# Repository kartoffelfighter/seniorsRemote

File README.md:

# seniorsRemote
A very basic remote tv (IR) control for seniors (and lazy people like me)

# nightly branch
this branch is dangerous! push -f(uck) possible

# hwtest branch

nightlier than nightly branch - WIP hwtest firmware

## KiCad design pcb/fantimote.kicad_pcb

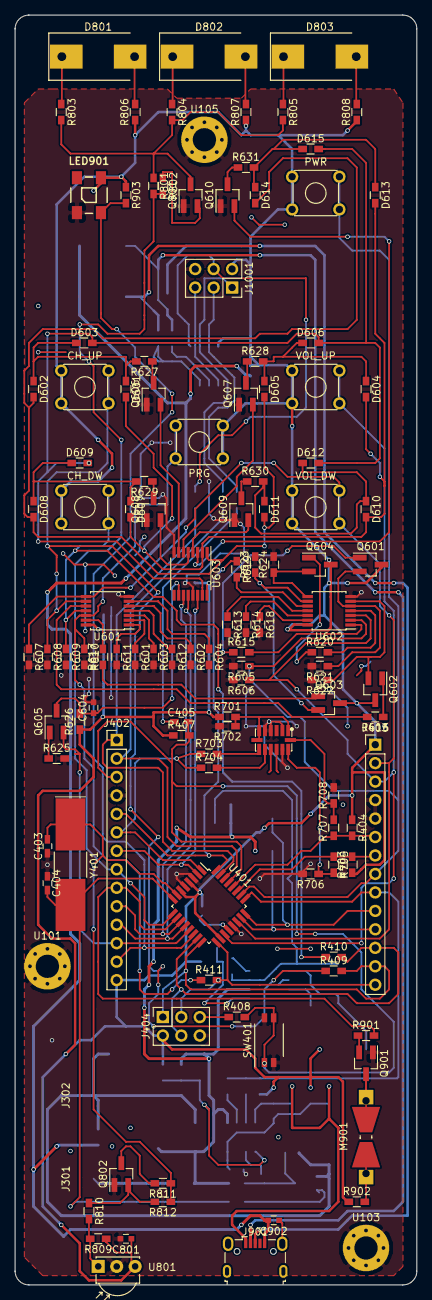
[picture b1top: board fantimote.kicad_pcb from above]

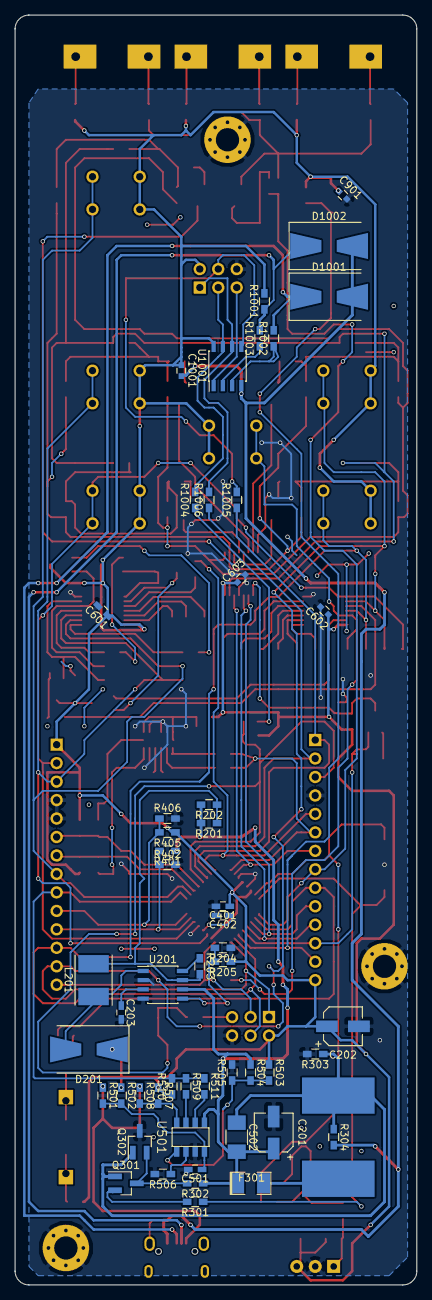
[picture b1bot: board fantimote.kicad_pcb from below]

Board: 2 copper layers, 55.2 x 174.6 mm, 176 parts (52 on the bottom side), 121 nets.

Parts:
C201: 10µ; CP_Elec_5x5.8
C202: 100µ; CP_Elec_5x5.8
C203: 1n; C_0603_HandSoldering
C401, C402, C501, C601: 100n; C_0603_HandSoldering
C403, C404: 10p; C_0603_HandSoldering
C405: 0,1µF; C_0603_HandSoldering
C502: 10µ; C_1210_HandSoldering
C602, C603, C801, C901, C1001: 100n; C_0603
C604: 1nF; C_0603
C902: 1µ; C_0603
CH_DW: SW_Push_Dual; SW_TH_Tactile_Omron_B3F-10xx
CH_UP: SW_Push_Dual; SW_TH_Tactile_Omron_B3F-10xx
D201: 1N5819; D_SMB-SMC_Universal_Handsoldering
D601, D602, D603, D604, D605, D606, D607, D608, D609, D610, D611, D612, D613, D614, D615: LED; R_0603_HandSoldering
D801, D802, D803: IR204A; D_SMC-RM10_Universal_Handsoldering
D1001, D1002: 3V6; D_SMB-SMC_Universal_Handsoldering
F301: Fuse; SMD-1210_Pol
IC701: ADXL345; ADXL3x5
J301: BAT+; SolderWirePad_single_SMD_5x10mm
J302: BAT-; SolderWirePad_single_SMD_5x10mm
J402: DIGITAL_DEBUG; Socket_Strip_Straight_1x14_Pitch2.54mm
J403: ANALOG_DEBUG; Socket_Strip_Straight_1x14_Pitch2.54mm
J404: ISP_atmega; Socket_Strip_Straight_2x03_Pitch2.54mm
J901: USB_OTG; USB_Micro-B_Wuerth-629105150521
J1001: ISP_tiny; Socket_Strip_Straight_2x03_Pitch2.54mm
L201: 68µH; L_Taiyo-Yuden_NR-50xx_HandSoldering
LED901: WS2812B
M901: Vibration_motor; Resistor_SMD+THTuniversal_0805to2512_RM10_HandSoldering
PRG: SW_Push_Dual; SW_TH_Tactile_Omron_B3F-10xx
PWR: SW_Push_Dual; SW_TH_Tactile_Omron_B3F-10xx
Q301, Q302, Q605, Q606, Q607, Q608, Q609, Q610, Q801, Q802, Q901: S8050; SOT-23_Handsoldering
Q601, Q602, Q603, Q604: BC807; SOT-23_Handsoldering
R201, R202: 0R5; R_0603_HandSoldering
R203: 180R; R_0603_HandSoldering
R204: 3k9; R_0603_HandSoldering
R205, R301, R302: 12k; R_0603_HandSoldering
R303, R304, R408, R409, R410, R411, R501, R505, R508, R619, R802, R806, R807, R808, R812, R901, R902, R1004, R1005, R1006: 0R0; R_0603_HandSoldering
R401, R402, R405, R406, R509, R510, R615, R616, R617, R620, R621, R622, R623, R624, R626, R705, R707, R903: 100k; R_0603_HandSoldering
R403, R404: 22k; R_0603_HandSoldering
R407, R601, R602, R603, R604, R605, R606, R607, R608, R609, R610, R611, R612, R613, R614, R618: 10k; R_0603_HandSoldering
R502, R503, R504, R625, R801, R811: N/A; R_0603_HandSoldering
R506: 2k0; R_0603_HandSoldering
R507: n/a; R_0603_HandSoldering
R511: 200k; R_0603_HandSoldering
R627, R628, R629, R630, R631: 470R; R_0603_HandSoldering
R701: 90k; R_0603_HandSoldering
R702, R706, R708: 45k; R_0603_HandSoldering
R703: INT1; R_0603_HandSoldering
R704: INT2; R_0603_HandSoldering
R803, R804, R805: 560R; R_0603_HandSoldering
R809: 24k; R_0603_HandSoldering
R810: 100R; R_0603_HandSoldering
R1001: 1k5; R_0603_HandSoldering
R1002, R1003: 68R; R_0603_HandSoldering
SW401: RESET; SW_DIP_x2_W6.15mm_Slide_Omron_A6H
U101, U103, U105: mounting_hole; MountingHole_3.2mm_M3_Pad_Via
U201: MC34063; SOIC-8_3.9x4.9mm_Pitch1.27mm
U401: ATMEGA328-AU; TQFP-32_7x7mm_Pitch0.8mm
U501: TPS4056; SOP-8
U601, U602: 74HC02; TSSOP-14_4.4x5mm_Pitch0.65mm
U603: 74HC595; TSSOP-16_4.4x5mm_Pitch0.65mm
U801: TSDP341xx; IRReceiver_Vishay_MOLD-3pin
U1001: ATTINY85; SOIC-8_3.9x4.9mm_Pitch1.27mm
VOL_DW: SW_Push_Dual; SW_TH_Tactile_Omron_B3F-10xx
VOL_UP: SW_Push_Dual; SW_TH_Tactile_Omron_B3F-10xx
Y401: Crystal; Crystal_SMD_SeikoEpson_MC405-2pin_9.6x4.1mm_HandSoldering

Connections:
+5V: C202.1, C401.1, C601.1, C602.1, C603.1, C801.1, C901.1, C1001.1, CH_DW.1, CH_DW.3, CH_UP.1, CH_UP.3, D201.1, J402.14, J403.1, J404.2, J1001.2, LED901.1, PRG.1, PRG.3, PWR.1, PWR.3, Q601.3, Q602.3, Q603.3, Q604.3, R205.1, R403.1, R404.1, R405.1, R407.1, R502.1, R503.1, R507.1, R510.1, R626.1, R701.1, R806.1, R807.1, R808.1, R809.1, R902.1, R903.1, R1001.2, U401.4, U401.6, U401.18, U601.14, U602.14, U603.16, U801.3, U1001.8, VOL_DW.1, VOL_DW.3, VOL_UP.1, VOL_UP.3
+5VD: J901.1, R501.1, R508.1
+BATT: C201.1, C502.2, F301.1, R201.2, R202.2, R302.1, R401.1, R504.1, U201.6, U501.5
-BATT: C502.1, J302.1, Q301.1, Q302.1, R303.1, R304.1
A0: J403.11, R401.2, R402.1, U401.23
A1: J403.10, R405.2, R406.1, U401.24
A2: J403.9, R509.1, R510.2, R511.1, U401.25
A3: J403.8, PWR.2, PWR.4, R605.1, U401.26, U602.2
A4: J403.7, R403.2, R705.1, U401.27
A5: J403.6, R404.2, R707.1, U401.28
A6: J403.3, R606.1, U401.19, U602.3, VOL_UP.2, VOL_UP.4
A7: J403.2, R607.1, U401.22, U601.8, VOL_DW.2, VOL_DW.4
CH_DW: CH_DW.2, CH_DW.4, R410.1, R609.1, U601.11
CH_UP: CH_UP.2, CH_UP.4, R409.1, R608.1, U601.9
D2: J402.5, R619.1, U401.32
D3: J402.6, R703.1, R704.1, U401.1
D4: J402.7, U401.2, U603.14
D5: J402.8, R801.2, R802.2, U401.9
D6: J402.9, R901.2, U401.10
D7: J402.10, U401.11, U603.11
D8: J402.11, U401.12, U603.12
D9: J402.12, Q605.2, U401.13
D10: J402.13, LED901.4, R903.2, U401.14
DTR: C405.1, R1004.1
GND: C201.2, C202.2, C203.2, C401.2, C402.2, C403.1, C404.1, C501.2, C601.2, C602.2, C603.2, C604.2, C801.2, C901.2, IC701.2, IC701.4, IC701.5, IC701.12, J402.4, J403.4, J403.5, J404.6, J1001.6, LED901.3, Q302.3, Q606.1, Q607.1, Q608.1, Q609.1, Q610.1, Q801.1, Q802.1, Q901.1, R204.1, R303.2, R402.2, R406.2, R505.2, R506.2, R601.2, R602.2, R603.2, R604.2, R605.2, R606.2, R607.2, R608.2, R609.2, R610.2, R611.2, R612.2, R613.2, R614.2, R618.2, R621.2, R622.2, R623.2, R624.2, R625.2, R702.2, R706.2, R708.2, SW401.2, SW401.4, U101.1, U103.1, U105.1, U201.2, U201.4, U401.3, U401.5, U401.21, U501.3, U601.7, U602.7, U603.8, U603.13, U801.2
GNDD: C902.2, C1001.2, D1001.2, D1002.2, J901.5, R304.2, U1001.4
IR_RECEIVE: C403.2, R811.1, R812.1, U401.7, Y401.1
MISO: J403.13, J404.1, R409.2, U401.16
MOSI: J403.12, J404.4, R410.2, U401.15
unnamed: C203.1, U201.3
unnamed: C402.1, U401.20
unnamed: C501.1, R501.2, R502.2, U501.4
unnamed: C604.1, Q605.3, R626.2, U603.10
unnamed: C902.1, J901.6
unnamed: D201.2, L201.1, U201.1
unnamed: D601.1, D602.1, D603.1, R627.2
unnamed: D601.2, D604.2, D607.2, D610.2, D613.2, U603.2
unnamed: D602.2, D605.2, D608.2, D611.2, D614.2, U603.1
unnamed: D603.2, D606.2, D609.2, D612.2, D615.2, U603.15
unnamed: D604.1, D605.1, D606.1, R628.2
unnamed: D607.1, D608.1, D609.1, R629.2
unnamed: D610.1, D611.1, D612.1, R630.2
unnamed: D613.1, D614.1, D615.1, R631.2
unnamed: D801.1, R803.1
unnamed: D801.2, R806.2
unnamed: D802.1, R804.1
unnamed: D802.2, R807.2
unnamed: D803.1, R805.1
unnamed: D803.2, R808.2
unnamed: F301.2, J301.1
unnamed: IC701.1, IC701.6, IC701.7, R701.2, R702.1
unnamed: IC701.8, R703.2
unnamed: IC701.9, R704.2
unnamed: IC701.13, R705.2, R706.1
unnamed: IC701.14, R707.2, R708.1
unnamed: J404.5, R408.1
unnamed: L201.2, R201.1, R202.1, R203.2, U201.7
unnamed: M901.1, R902.2
unnamed: M901.2, Q901.3
unnamed: Q301.2, R301.2
unnamed: Q301.3, Q302.2, R302.2
unnamed: Q601.1, R615.1
unnamed: Q601.2, R621.1, U602.5
unnamed: Q602.1, R616.1
unnamed: Q602.2, R622.1, U602.6
unnamed: Q603.1, R617.1
unnamed: Q603.2, R623.1, U602.9
unnamed: Q604.1, R620.1
unnamed: Q604.2, R624.1, U602.8
unnamed: Q605.1, R625.1
unnamed: Q606.2, U603.7
unnamed: Q606.3, R627.1
unnamed: Q607.2, U603.6
unnamed: Q607.3, R628.1
unnamed: Q608.2, U603.5
unnamed: Q608.3, R629.1
unnamed: Q609.2, U603.4
unnamed: Q609.3, R630.1
unnamed: Q610.2, U603.3
unnamed: Q610.3, R631.1
unnamed: Q801.2, R802.1
unnamed: Q801.3, R801.1, R803.2, R804.2, R805.2
unnamed: Q802.2, R810.1, R812.2
unnamed: Q802.3, R811.2
unnamed: Q901.2, R901.1
unnamed: R203.1, U201.8
unnamed: R204.2, R205.2, U201.5
unnamed: R503.2, R504.2, R505.1, U501.1
unnamed: R506.1, U501.2
unnamed: R507.2, R508.2, U501.8
unnamed: R509.2, U501.7
unnamed: R511.2, U501.6
unnamed: R601.1, U601.2
unnamed: R602.1, U601.5
unnamed: R603.1, U601.3
unnamed: R604.1, U601.6
unnamed: R611.1, U601.1
unnamed: R612.1, U601.4
unnamed: R613.1, U602.11
unnamed: R614.1, U602.12
unnamed: R615.2, U602.1
unnamed: R616.2, U601.10
unnamed: R617.2, U601.13
unnamed: R618.1, U602.13
unnamed: R619.2, U602.10
unnamed: R620.2, U602.4
unnamed: R809.2, R810.2, U801.1
unnamed: R1002.1, U1001.3
unnamed: R1003.1, U1001.2
PB7: C404.2, R301.1, U401.8, Y401.2
PRG: PRG.2, PRG.4, R411.1, R610.1, U601.12
RESET: C405.2, J402.3, R407.2, R408.2, SW401.1, SW401.3, U401.29
RXI: J402.2, R1006.1, U401.30
SCK: J403.14, J404.3, R411.2, U401.17
TXD: J402.1, R1005.1, U401.31
USB_D+: D1001.1, J901.3, R1002.2
USB_D-: D1002.1, J901.2, R1001.1, R1003.2
tiny_MISO: J1001.1, R1006.2, U1001.6
tiny_MOSI: J1001.4, R1005.2, U1001.5
tiny_RESET: J1001.5, U1001.1
tiny_SCK: J1001.3, R1004.2, U1001.7

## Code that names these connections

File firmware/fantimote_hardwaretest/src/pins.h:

// pin definition for layout v1 Debug (08/18)

#define ISR_BUTTON 2    // PD2      ISR IN
#define ISR_ADXL 3      // PD3      ISR IN
#define ring_led_data 4    // PD4   OUT
#define IR_SEND 5          // PD5   PWM OUT
#define vibrate 6          // PD6   PWM OUT
#define ring_led_clock 7   //  PD7  OUT
#define ring_led_clock_2 8     // PB0 OUT
#define ring_led_reset 9        // PB1 OUT
#define WS2812Bpin 10           // PB2 OUT
#define IR_RECEIVE PB6          // PB6 IN
#define killSwitch PB7          // PB7 OUT

#define meausre_vbat A0         // PC0 ADC IN
#define measure_vplus A1        // PC1 ADC IN
#define CHARGE A2               // PC2 ADC IN
#define PWR A3                  // PC3 IN
#define ADXL_DATA A4            // PC4 SDA IO
#define ADXL_CLK A5             // PC5 SCL IO
#define VOL_UP A6               // PC6 IN
#define VOL_DW A7               // PC7 IN


// needed for programming porpuse
#define CH_UP PB4
#define CH_DW PB3
#define PRG PB5

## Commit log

2018-07-07 ADXL integration
2018-07-07 WIP: prototype PCB
2018-07-13 Update issue templates
2018-07-13 nightly | pcb build, routing, placing
2018-07-14 routing
2018-07-14 nightly readme
2018-07-27 first firmware testing with adxl dev board
2018-07-27 new routes, changed few parts for shorter tracks
2018-07-29 new components list with changed footprints
2018-07-29 WIP: large amount of new routes, removed testpoints
2018-07-31 imported 3d files from pcb
2018-07-31 gerber files for factoring at allpcb
2018-07-31 added 3d files, added routes, added copper layers, added silkscreen
2018-07-31 3d files for case
2018-08-15 possible bootloader
2018-08-15 basic documentation
2018-08-15 hardwaretest with arduino bootloader
2018-08-15 hardwaretest for bare atmega without arduino
2018-08-18 docs for pcb
2018-08-18 right configured interrupts now
2018-08-18 seperate header file for main
2018-08-18 excluded header and config, integrated 1mS timer function
2018-08-18 new files
2018-08-18 new config file
2018-08-18 feedback led relevant code
2018-08-18 timer description
2018-08-18 hwtest description
2018-09-08 updated ignore template
2018-09-08 new config handling
2018-09-08 ir receiver relevant code
2018-09-08 cleaned up main
2018-09-08 hard coded storage conditions
2018-09-08 ws led bit banger to control UX led
2018-09-08 librarys for adxl controller and iic
